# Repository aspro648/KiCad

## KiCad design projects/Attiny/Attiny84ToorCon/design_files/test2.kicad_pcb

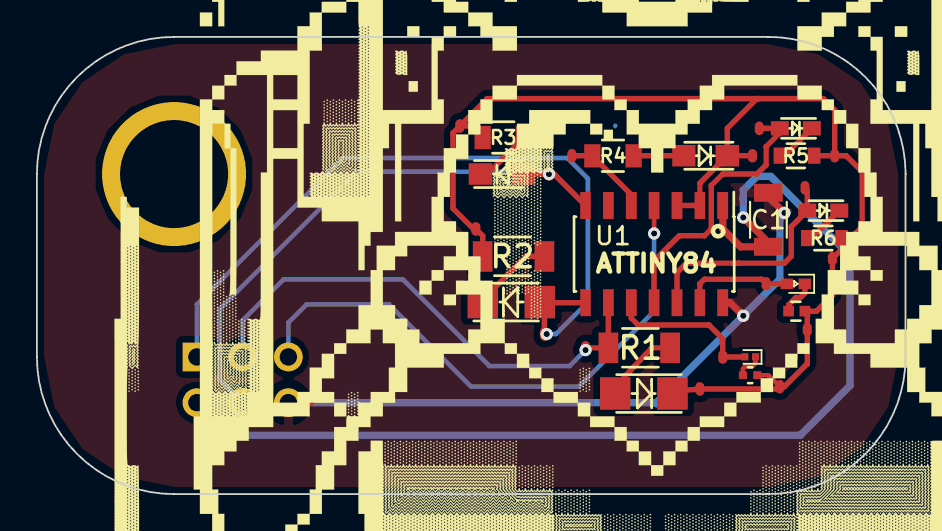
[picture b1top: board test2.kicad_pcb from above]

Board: 2 copper layers, 48.3 x 25.4 mm, 36 parts (1 on the bottom side), 20 nets.

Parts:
C1: 0.1 uF; C_1206
CON1: AVR-ISP-6
D1, D2: LED; LED-1206
D3, D4: LED; LED-0805
D5, D6: LED; LED-0603
D7: LED; LED_0402
D8: LED; LED_0201
P0: CONN_01X01; Pin_Header_Straight_1x01
P2, P3, P4, P5, P6, P7, P8, P9: CONN_01X01; testPad
PG1, PG2, PG3, PG4, PG5, PG6, PG7, PG8: CONN_01X01; testPad
R1, R2: 100; R_1206
R3, R4: 100; R_0805
R5, R6: 100; R_0603
R7: 100; R_0402
R8: 100; R_0201
U1: ATTINY84A-SSU; SOIC-14_3.9x8.7mm_Pitch1.27mm

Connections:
+BATT: C1.1, CON1.2, U1.1
/MISO: CON1.1, D2.2, P3.1, U1.8
/MOSI: CON1.4, D3.2, P4.1, U1.7
/RESET: CON1.5, U1.4
/SCK: CON1.3, P2.1, R1.1, U1.9
GND: C1.2, CON1.6, U1.14
unnamed: D1.1, D4.1, PG1.1, PG2.1, PG3.1, PG4.1, PG5.1, PG6.1, PG7.1, PG8.1, R2.2, R3.2, R5.2, R6.2, R7.2, R8.2, U1.2, U1.3
unnamed: D1.2, R1.2
unnamed: D2.1, R2.1
unnamed: D3.1, R3.1
unnamed: D4.2, R4.2
unnamed: D5.1, R5.1
unnamed: D5.2, P6.1, U1.11
unnamed: D6.1, R6.1
unnamed: D6.2, P7.1, U1.12
unnamed: D7.1, R7.1
unnamed: D7.2, P8.1, U1.13
unnamed: D8.1, R8.1
unnamed: D8.2, P9.1, U1.10
unnamed: P5.1, R4.1, U1.5

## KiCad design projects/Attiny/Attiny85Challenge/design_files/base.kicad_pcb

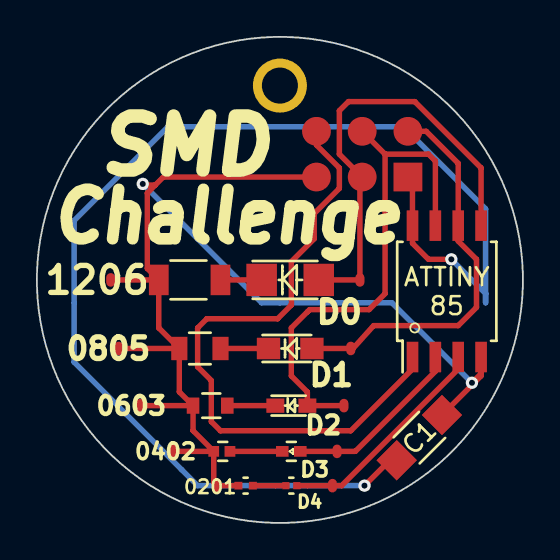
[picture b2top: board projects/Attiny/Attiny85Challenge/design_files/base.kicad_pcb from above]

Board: 2 copper layers, 27.0 x 27.0 mm, 25 parts (1 on the bottom side), 13 nets.

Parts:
BT1: Battery; BATT_CR2032_SMD
C1: 0.1 uF; C_1206_HandSoldering
CON1: AVR-ISP-6
D0: LED; LED-1206
D1: LED; LED-0805
D2: LED; LED-0603
D3: LED; LED_0402
D4: LED; LED_0201
IC1: IC1; SOIJ-8_5.3x5.3mm_Pitch1.27mm
P0, P1, P2, P3, P4: CONN_01X01; testPad
P5: CONN_01X01; Pin_Header_Straight_1x01
PG0, PG1, PG2, PG3, PG4: CONN_01X01; testPad
R0: 330; R_1206
R1: 330; R_0805
R2: 330; R_0603
R3: 330; R_0402
R4: 330; R_0201

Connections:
+BATT: BT1.1, C1.2, CON1.2, IC1.8
GND: BT1.2, C1.1, CON1.6, IC1.4, PG0.1, PG1.1, PG2.1, PG3.1, PG4.1, R0.2, R1.2, R2.2, R3.2, R4.2
unnamed: CON1.1, D1.2, IC1.6, P1.1
unnamed: CON1.3, D2.2, IC1.7, P2.1
unnamed: CON1.4, D0.2, IC1.5, P0.1
unnamed: CON1.5, IC1.1
unnamed: D0.1, R0.1
unnamed: D1.1, R1.1
unnamed: D2.1, R2.1
unnamed: D3.1, R3.1
unnamed: D3.2, IC1.2, P3.1
unnamed: D4.1, R4.1
unnamed: D4.2, IC1.3, P4.1

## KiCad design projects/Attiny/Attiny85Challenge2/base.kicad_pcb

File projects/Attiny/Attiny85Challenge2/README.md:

Introduction
============

Test your surface mount soldering skills out, starting with a 1206 package and work your way down into an oblivion of frustration. Powered by a CR2032 coin cell and Attiny 85 SOIC. Be warned that trying to hand solder a 0201 package, which is just slightly larger than a grain of sand, may be considered evidence of insanity and get you committed to bad places by your loved ones and/or arch nemesis.I have submitted to request from miserable people to make this an unfortunate kit. Don't think I'm doing you any favors: https://www.tindie.com/products/MakersBox/smd-challenge/

Bill Of Materials
=================
  
- 1 ea., Perfect Purple PCB from OSH Park, https://oshpark.com/shared_projects/UFefat4N
- 1 ea., Atmel ATTINY25V-10SNR, Digikey 1611-ATTINY25V-10SNRCT-ND
- 1 ea., CAP CER 0.1UF 50V X7R 1206, KEMET C1206C104K5RAC7867, https://www.digikey.com/short/32vmjq
- 1 ea., LED RED CLEAR 1206 SMD, Lite-On LTST-C150KRKT, https://www.digikey.com/short/3253m7
- 1 ea., RES SMD 100 OHM 5% 1/4W 1206, Digiket P100ECT-ND
- 1 ea., LED ORANGE CLEAR 0805 SMD, https://www.digikey.com/short/qjwthb
- 1 ea., RES SMD 100 OHM 5% 1/8W 0805, https://www.digikey.com/short/z7nv19
- 1 ea., LED YELLOW CLEAR 0603 SMD, Lite-On LTST-C191KSKT, https://www.digikey.com/short/3wzzr2
- 1 ea., RES SMD 100 OHM 5% 1/10W 0603, https://www.digikey.com/short/z7n1cv
- 1 ea., LED GREEN CLEAR 0402 SMD, SunLED XZVG68W-2, https://www.digikey.com/short/3wzzfm
- 1 ea., RES 100 OHM 5% 1/16W 0402, https://www.digikey.com/short/z7n132
- 1 ea., LED BLUE CLEAR 0201 SMD, Kingbright APG0603PBC-TT-5MAV, https://www.digikey.com/short/3wzzfr
- 1 ea., RES SMD 100 OHM 5% 1/20W 0201, https://www.digikey.com/short/z7n18r
- 1 ea. SMD Battery holder, Linx BAT-HLD-001, Digikey BAT-HLD-001-ND
- 1 ea. CR2032 Battery, Panasonic CR2032, Digikey P189-ND (requires ground shipping, or buy locally).

Design Files
============
This project is designed using Open Source [KiCad](http://kicad-pcb.org/). Design files are located in the [design_files](design_files/) folder.  You can oogle the [schematic](images/project.sch.png).

Firmware
========
This project is programed using the Open Source [Arduino](https://www.arduino.cc/). I use my Open Source [AVR Programming Shield](https://www.tindie.com/products/MakersBox/yet-another-programming-shield/) to program the Attiny. The firmware is located in the [firmware](firmware/) folder.

Assembly Instructions
=====================
I have posted [minimal instructions at HackADay](https://hackaday.io/project/25265-an-unfortunate-smd-project).

License
=======
[Attribution-ShareAlike 3.0 United States (CC BY-SA 3.0 US)](https://creativecommons.org/licenses/by-sa/3.0/us/)

You are free to:

- Share — copy and redistribute the material in any medium or format
- Adapt — remix, transform, and build upon the material

Under the following terms:

- Attribution — You must give appropriate credit, provide a link to the license, and indicate if changes were made. You may do so in any reasonable manner, but not in any way that suggests the licensor endorses you or your use.
- ShareAlike — If you remix, transform, or build upon the material, you must distribute your contributions under the same license as the original.

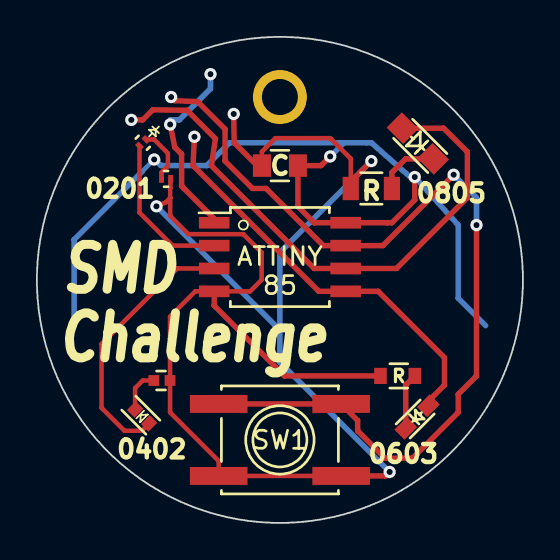
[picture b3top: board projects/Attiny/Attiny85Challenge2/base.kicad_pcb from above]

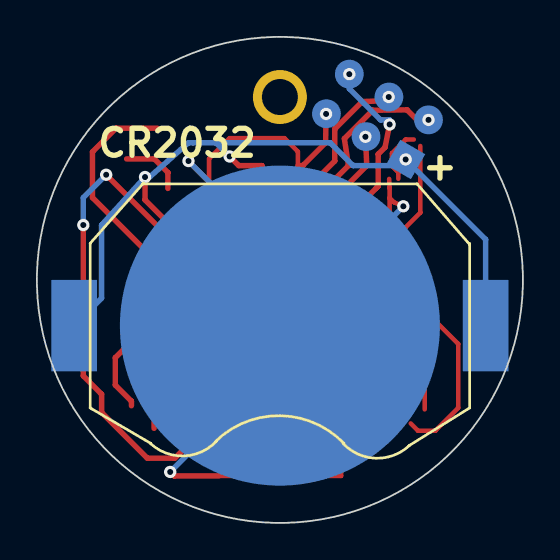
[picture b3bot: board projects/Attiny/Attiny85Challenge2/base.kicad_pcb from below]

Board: 2 copper layers, 27.0 x 27.0 mm, 14 parts (2 on the bottom side), 12 nets.

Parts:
BT1: Battery; BATT_CR2032_SMD
C1: 0.1 uF; C_0805
CON1: AVR-ISP-6
D0, D4: LED; LED-0603
D1: LED; LED-0805
D3: LED; R_0201
IC1: ATTINY85-S; SOIJ-8_5.3x5.3mm_Pitch1.27mm
P1: CONN_01X01; Pin_Header_Straight_1x01
R1: 330; R_0805
R2: 330; R_0603
R3: 330; R_0402
R4: 330; R_0201
SW1: SW_PUSH; SW_SPST_EVQQ2

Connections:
+BATT: BT1.1, C1.2, CON1.2, IC1.8
GND: BT1.2, C1.1, CON1.6, IC1.4, R1.2, R2.2, R3.2, R4.2, SW1.2
unnamed: CON1.1, D1.2, IC1.6
unnamed: CON1.3, IC1.7, SW1.1
unnamed: CON1.4, D0.2, IC1.5
unnamed: CON1.5, IC1.1
unnamed: D0.1, R2.1
unnamed: D1.1, R1.1
unnamed: D3.1, R4.1
unnamed: D3.2, IC1.2
unnamed: D4.1, R3.1
unnamed: D4.2, IC1.3

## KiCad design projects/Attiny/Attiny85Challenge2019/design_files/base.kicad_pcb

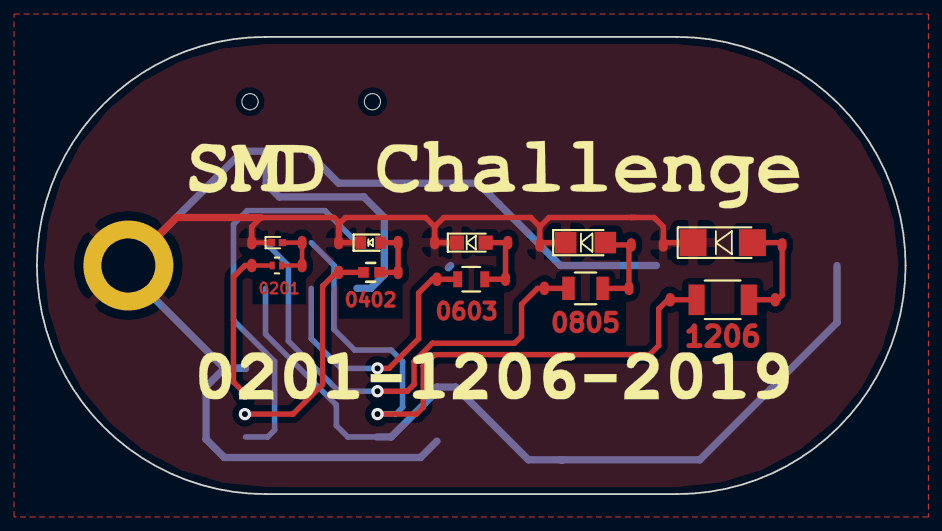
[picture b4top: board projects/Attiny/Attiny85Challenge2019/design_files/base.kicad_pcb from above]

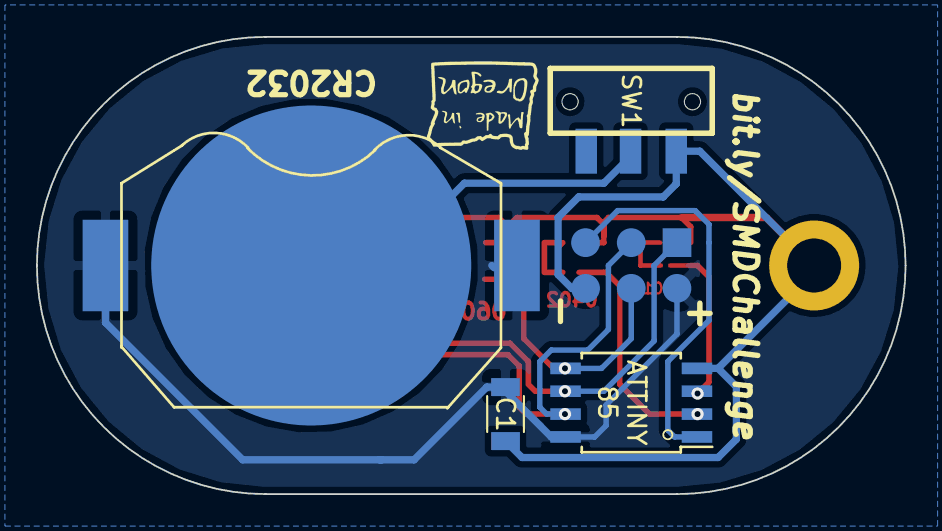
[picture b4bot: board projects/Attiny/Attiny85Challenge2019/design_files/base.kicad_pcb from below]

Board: 2 copper layers, 48.3 x 25.4 mm, 37 parts (5 on the bottom side), 14 nets.

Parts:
BT1: Battery; BATT_CR2032_SMD
C1: 0.1 uF; C_1206
CON1: AVR-ISP-6
D0: LED; LED_1206
D1: LED; LED_0805
D2: LED; LED_0603
D3: LED; LED_0402
D4: LED; LED_0201
IC1: IC1; SOIJ-8_5.3x5.3mm_Pitch1.27mm
J1, J2, J3, J3#2, J4, J4#2, J5, J6, J7, J8, J9, J10, J10#2, J11, J11#2, J12, J12#2, J13, J14, J15: Conn_01x01; testPad
P5: CONN_01X01; Pin_Header_Straight_1x01
R0: 330; R_1206
R1: 330; R_0805
R2: 330; R_0603
R3: 330; R_0402
R4: 330; R_0201
SW1: SW_Push_SPDT; SPST_SMD
VAL: MadeInOregonRev25

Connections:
+BATT: BT1.1, C1.2, CON1.2, IC1.8
GND: C1.1, CON1.6, D0.1, D1.1, D2.1, D3.1, D4.1, IC1.4, J5.1, J6.1, J13.1, J14.1, J15.1, P5.1, SW1.1
unnamed: BT1.2, SW1.2
unnamed: CON1.1, IC1.6, J8.1, R1.1
unnamed: CON1.3, IC1.7, J7.1, R0.1
unnamed: CON1.4, IC1.5, J9.1, R2.1
unnamed: CON1.5, IC1.1
unnamed: D0.2, J10.1, J10#2.1, R0.2
unnamed: D1.2, J11.1, J11#2.1, R1.2
unnamed: D2.2, J12.1, J12#2.1, R2.2
unnamed: D3.2, J3.1, J3#2.1, R3.2
unnamed: D4.2, J4.1, J4#2.1, R4.2
unnamed: IC1.2, J1.1, R3.1
unnamed: IC1.3, J2.1, R4.1

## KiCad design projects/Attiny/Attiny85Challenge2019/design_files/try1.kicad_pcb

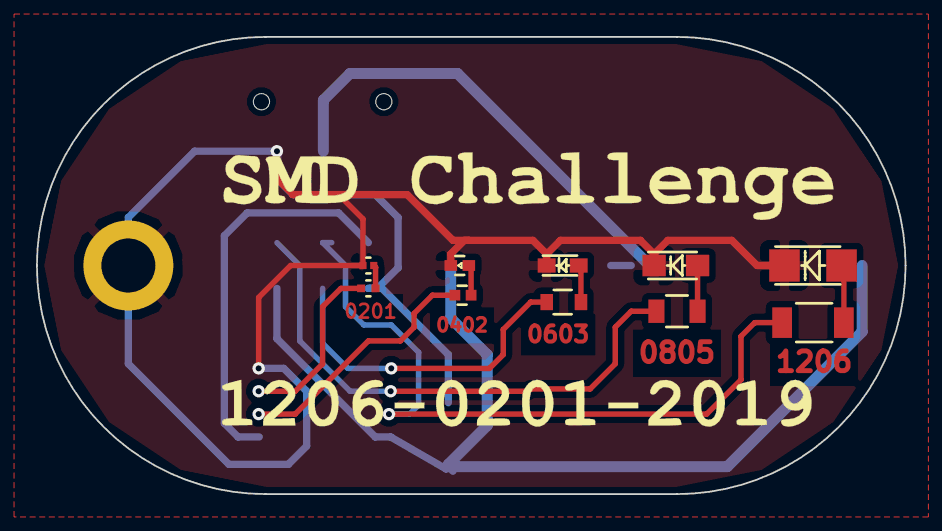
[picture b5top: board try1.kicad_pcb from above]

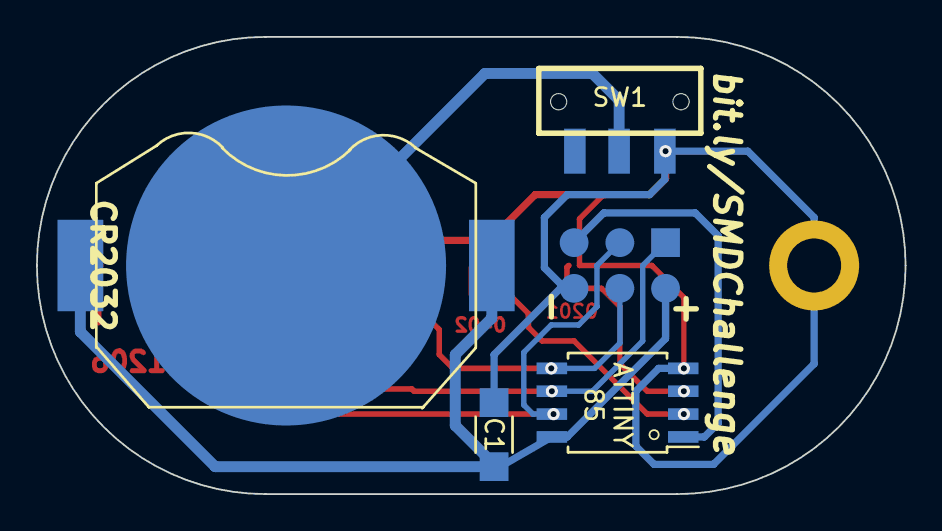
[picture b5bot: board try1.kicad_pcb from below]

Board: 2 copper layers, 48.3 x 25.4 mm, 16 parts (5 on the bottom side), 14 nets.

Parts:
BT1: Battery; BATT_CR2032_SMD
C1: 0.1 uF; C_1206_HandSoldering
CON1: AVR-ISP-6
D0: LED; LED-1206
D1: LED; LED-0805
D2: LED; LED-0603
D3: LED; LED_0402
D4: LED; LED_0201
IC1: IC1; SOIJ-8_5.3x5.3mm_Pitch1.27mm
P5: CONN_01X01; Pin_Header_Straight_1x01
R0: 330; R_1206
R1: 330; R_0805
R2: 330; R_0603
R3: 330; R_0402
R4: 330; R_0201
SW1: SW_Push_SPDT; SPST_SMD

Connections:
+BATT: BT1.1, C1.2, CON1.2, IC1.8
GND: C1.1, CON1.6, D0.1, D1.1, D2.1, D3.1, D4.1, IC1.4, P5.1, SW1.1
unnamed: BT1.2, SW1.2
unnamed: CON1.1, IC1.6, R1.1
unnamed: CON1.3, IC1.7, R0.1
unnamed: CON1.4, IC1.5, R2.1
unnamed: CON1.5, IC1.1
unnamed: D0.2, R0.2
unnamed: D1.2, R1.2
unnamed: D2.2, R2.2
unnamed: D3.2, R3.2
unnamed: D4.2, R4.2
unnamed: IC1.2, R3.1
unnamed: IC1.3, R4.1
